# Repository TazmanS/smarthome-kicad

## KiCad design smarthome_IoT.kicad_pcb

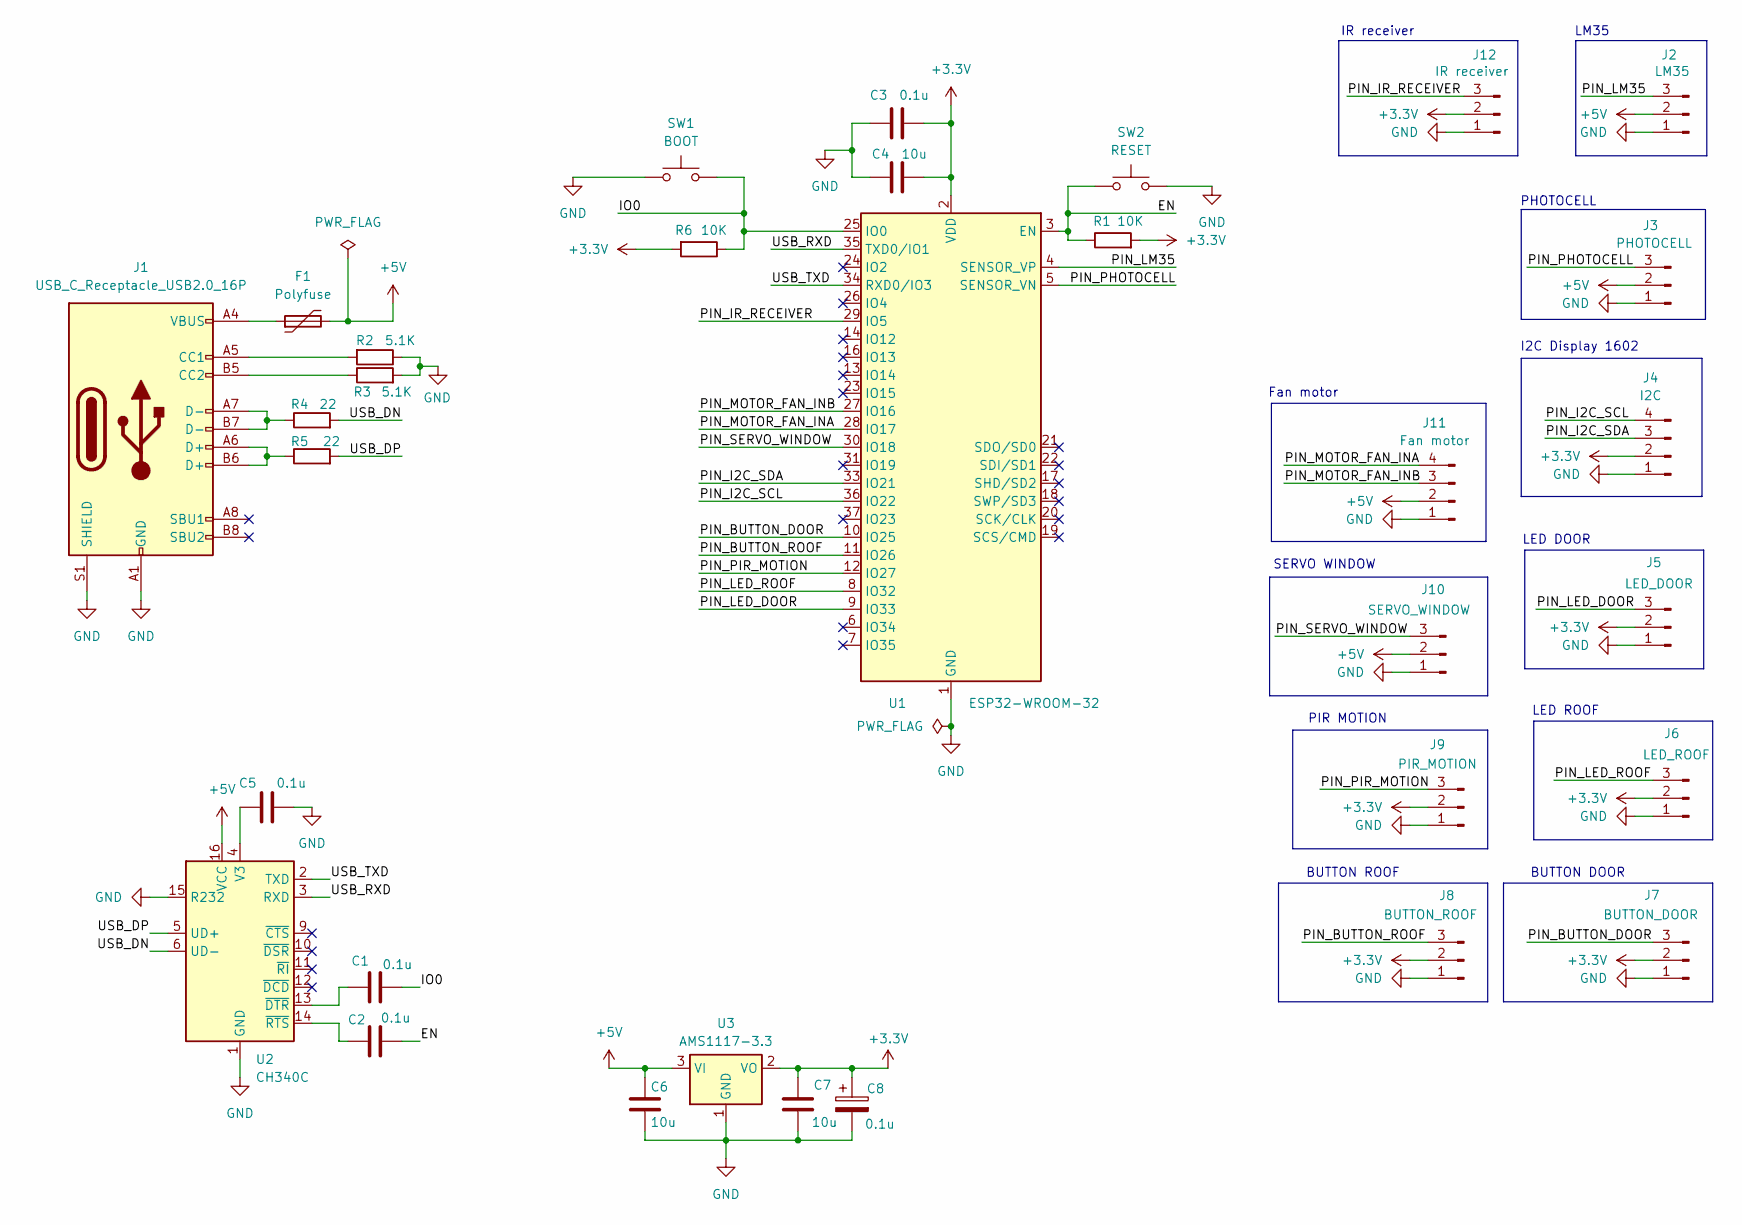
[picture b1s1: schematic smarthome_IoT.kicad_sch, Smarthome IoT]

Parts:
C1, C2, C3, C5, C8: 0.1u; C_0805_2012Metric_Pad1.18x1.45mm_HandSolder
C4, C6, C7: 10u; C_1206_3216Metric_Pad1.33x1.80mm_HandSolder
F1: Polyfuse; Fuse_1206_3216Metric_Pad1.42x1.75mm_HandSolder
J1: USB_C_Receptacle_USB2.0_16P; USB_C_Receptacle_GCT_USB4105-xx-A_16P_TopMnt_Horizontal
J2: LM35; PinHeader_1x03_P2.54mm_Vertical
J3: PHOTOCELL; PinHeader_1x03_P2.54mm_Vertical
J4: I2C; PinHeader_1x04_P2.54mm_Vertical
J5: LED_DOOR; PinHeader_1x03_P2.54mm_Vertical
J6: LED_ROOF; PinHeader_1x03_P2.54mm_Vertical
J7: BUTTON_DOOR; PinHeader_1x03_P2.54mm_Vertical
J8: BUTTON_ROOF; PinHeader_1x03_P2.54mm_Vertical
J9: PIR_MOTION; PinHeader_1x03_P2.54mm_Vertical
J10: SERVO_WINDOW; PinHeader_1x03_P2.54mm_Vertical
J11: Fan motor; PinHeader_1x04_P2.54mm_Vertical
J12: IR receiver; PinHeader_1x03_P2.54mm_Vertical
R1, R6: 10K; R_0805_2012Metric_Pad1.20x1.40mm_HandSolder
R2, R3: 5.1K; R_0805_2012Metric_Pad1.20x1.40mm_HandSolder
R4, R5: 22; R_0805_2012Metric_Pad1.20x1.40mm_HandSolder
SW1: BOOT; SW_SPST_TL3342
SW2: RESET; SW_SPST_TL3342
U1: ESP32-WROOM-32
U2: CH340C; SOIC-16_3.9x9.9mm_P1.27mm
U3: AMS1117-3.3; SOT-223-3_TabPin2

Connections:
+3.3V: C3.2, C4.2, C7.1, C8.1, J4.2, J5.2, J6.2, J7.2, J8.2, J9.2, J12.2, R1.2, R6.2, U1.2 (VDD), U3.2 (VO)
+5V: C6.1, F1.2, J2.2, J3.2, J10.2, J11.2, U2.16 (VCC), U3.3 (VI)
/EN: C2.2, R1.1, SW2.1, U1.3 (EN); also elsewhere on the board
/IO0: C1.1, R6.1, SW1.2, U1.25 (IO0); also elsewhere on the board
/PIN_BUTTON_DOOR: J7.3, U1.10 (IO25)
/PIN_BUTTON_ROOF: J8.3, U1.11 (IO26)
/PIN_I2C_SCL: J4.4, U1.36 (IO22)
/PIN_I2C_SDA: J4.3, U1.33 (IO21)
/PIN_IR_RECEIVER: J12.3, U1.29 (IO5)
/PIN_LED_DOOR: J5.3, U1.9 (IO33)
/PIN_LED_ROOF: J6.3, U1.8 (IO32)
/PIN_LM35: J2.3, U1.4 (SENSOR_VP)
/PIN_MOTOR_FAN_INA: J11.4, U1.28 (IO17)
/PIN_MOTOR_FAN_INB: J11.3, U1.27 (IO16)
/PIN_PHOTOCELL: J3.3, U1.5 (SENSOR_VN)
/PIN_PIR_MOTION: J9.3, U1.12 (IO27)
/PIN_SERVO_WINDOW: J10.3, U1.30 (IO18)
/USB_DN: R4.2, U2.6 (UD-)
/USB_DP: R5.2, U2.5 (UD+)
/USB_RXD: U1.35 (TXD0/IO1), U2.3 (RXD)
/USB_TXD: U1.34 (RXD0/IO3), U2.2 (TXD)
GND: C3.1, C4.1, C5.2, C6.2, C7.2, C8.2, J1.A1 (GND), J1.A12 (GND), J1.B1 (GND), J1.B12 (GND), J1.S1 (SHIELD), J2.1, J3.1, J4.1, J5.1, J6.1, J7.1, J8.1, J9.1, J10.1, J11.1, J12.1, R2.1, R3.2, SW1.1, SW2.2, U1.1 (GND), U1.15 (GND), U1.38 (GND), U1.39 (GND), U2.1 (GND), U2.15 (R232), U3.1 (GND); also elsewhere on the board
unnamed 22: F1.1, J1.A4 (VBUS), J1.A9 (VBUS), J1.B4 (VBUS), J1.B9 (VBUS); also elsewhere on the board
unnamed 23: J1.A5 (CC1), R2.2; also elsewhere on the board
unnamed 24: J1.B5 (CC2), R3.1; also elsewhere on the board
unnamed 25: J1.A6 (D+), J1.B6 (D+), R5.1; also elsewhere on the board
unnamed 26: J1.A7 (D-), J1.B7 (D-), R4.1; also elsewhere on the board
unnamed: C5.1, U2.4 (V3)
unnamed: C1.2, U2.13 (~DTR)
unnamed: C2.1, U2.14 (~RTS)

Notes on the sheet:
SERVO WINDOW
I2C Display 1602
PIR MOTION
LED ROOF
LED DOOR
IR receiver
LM35
BUTTON ROOF
PHOTOCELL
BUTTON DOOR
Fan motor

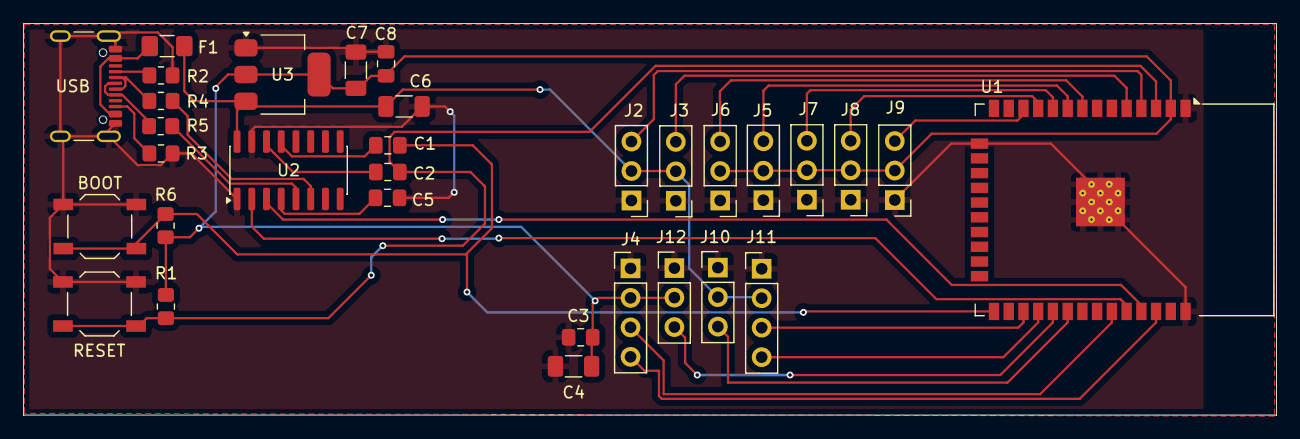
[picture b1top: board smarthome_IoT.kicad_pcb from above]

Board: 2 copper layers, 108.0 x 33.8 mm, 32 parts (0 on the bottom side), 30 nets.

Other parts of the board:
BOOT: BOOT; SW_SPST_TL3342
RESET: RESET; SW_SPST_TL3342
USB: USB_C_Receptacle_USB2.0_16P; USB_C_Receptacle_GCT_USB4105-xx-A_16P_TopMnt_Horizontal

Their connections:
/EN: RESET.1; also elsewhere on the board
/IO0: BOOT.2; also elsewhere on the board
GND: BOOT.1, RESET.2, USB.A1 (GND), USB.A12 (GND), USB.B1 (GND), USB.B12 (GND), USB.S1 (SHIELD); also elsewhere on the board
unnamed 22: USB.A4 (VBUS), USB.A9 (VBUS), USB.B4 (VBUS), USB.B9 (VBUS); also elsewhere on the board
unnamed 23: USB.A5 (CC1); also elsewhere on the board
unnamed 24: USB.B5 (CC2); also elsewhere on the board
unnamed 25: USB.A6 (D+), USB.B6 (D+); also elsewhere on the board
unnamed 26: USB.A7 (D-), USB.B7 (D-); also elsewhere on the board

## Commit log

2026-04-28 create project
2026-04-28 add screens
